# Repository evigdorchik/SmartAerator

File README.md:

# SmartAerator
Code for smart aerator used to nudge people into using less energy

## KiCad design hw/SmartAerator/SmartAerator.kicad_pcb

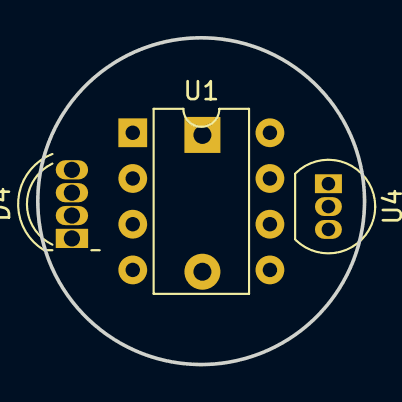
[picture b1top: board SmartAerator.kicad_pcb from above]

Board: 2 copper layers, 18.2 x 18.2 mm, 4 parts (1 on the bottom side), 7 nets, no tracks yet.

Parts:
BZ1: Buzzer; Buzzer_12x9.5RM7.6
D4: LED_RGBK; LED_D5.0mm-4_RGB
U1: ATtiny85-20P; DIP-8_W7.62mm
U4: LM35-LP; TO-92_Inline

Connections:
+3.3V: U1.8 (VCC), U4.1 (+V_{S})
GND: BZ1.2 (+), D4.4 (K), U1.4 (GND), U4.3 (GND)
unnamed: BZ1.1 (-), U1.2 (XTAL1/PB3)
unnamed: D4.3 (BA), U1.5 (AREF/PB0)
unnamed: D4.2 (GA), U1.6 (PB1)
unnamed: D4.1 (RA), U1.7 (PB2)
unnamed: U1.3 (XTAL2/PB4), U4.2 (V_{OUT})
